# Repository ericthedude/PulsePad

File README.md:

# PulsePad
A macropad made for HackClub's Hackpad project

Incudes 4 reprogrammable macro switches and 1 reprogrammable knob

This is my first time creating something from scratch. This is also my first time using github.

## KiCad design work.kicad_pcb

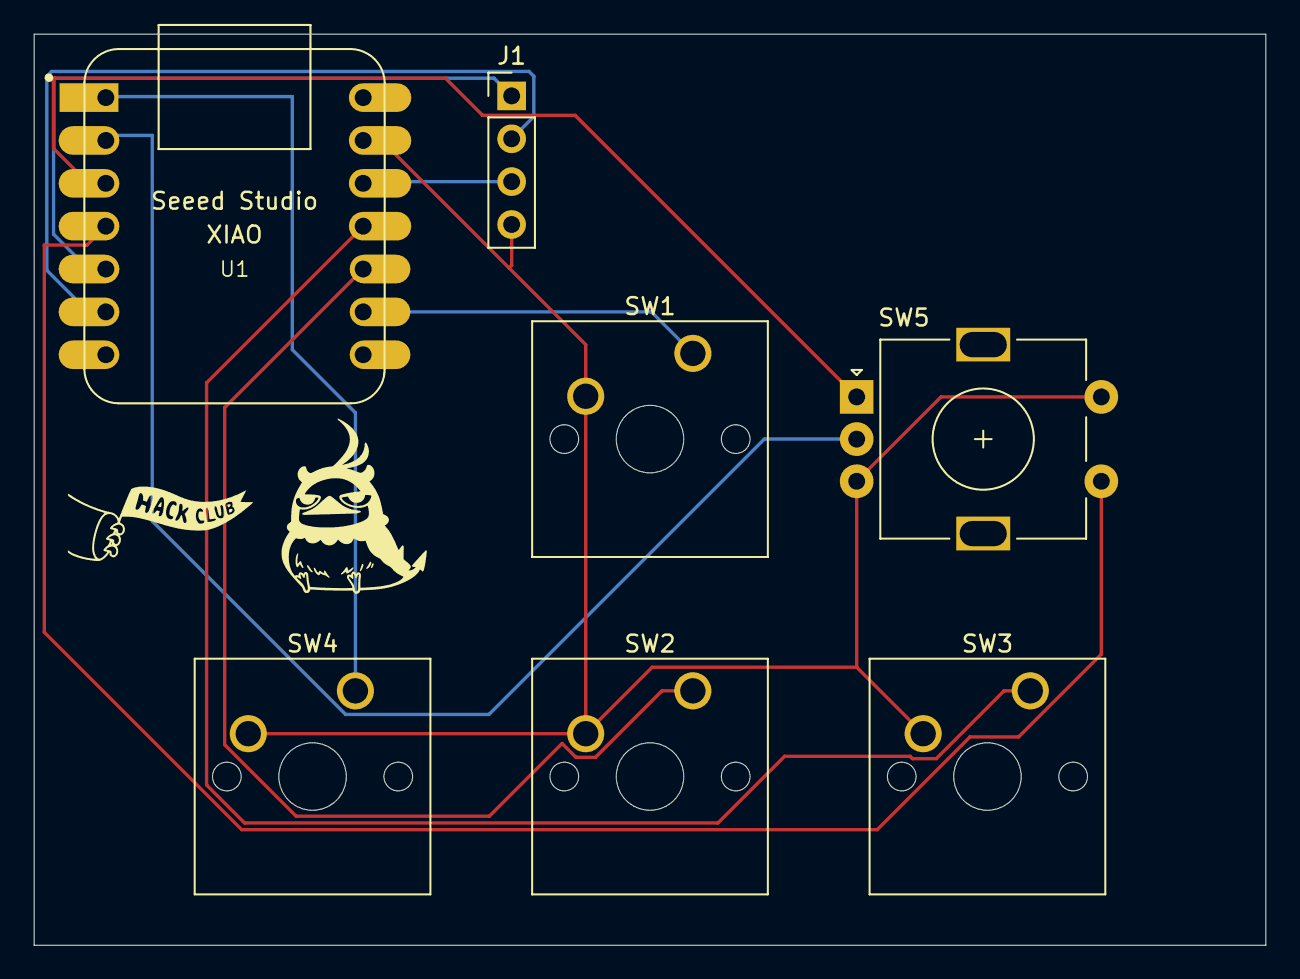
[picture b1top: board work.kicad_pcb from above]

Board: 2 copper layers, 73.0 x 54.0 mm, 7 parts (0 on the bottom side), 11 nets.

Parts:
J1: Conn_01x04_Pin; PinHeader_1x04_P2.54mm_Vertical
SW1: SW_Push_45deg; SW_Cherry_MX_1.00u_PCB
SW2, SW3, SW4: SW_Push_45deg; SW_Cherry_MX_1.50u_PCB
SW5: RotaryEncoder_Switch; RotaryEncoder_Alps_EC11E-Switch_Vertical_H20mm
U1: MOUDLE-SEEEDUINO-XIAO; XIAO-Generic-Hybrid-14P-2.54-21X17.8MM

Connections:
GND: J1.Ground (Pin_4_4), SW1.2, SW2.2, SW3.2, SW4.2, SW5.B, SW5.S2, U1.13 (GND)
unnamed: J1.1 (Pin_1_1), U1.5 (PA8_A4_D4_SDA)
unnamed: J1.2 (Pin_2_2), U1.6 (PA9_A5_D5_SCL)
unnamed: J1.3 (Pin_3_3), U1.12 (3V3)
unnamed: SW4.1, U1.1 (PA02_A0_D0)
unnamed: SW5.C, U1.2 (PA4_A1_D1)
unnamed: SW2.1, U1.10 (PA5_A9_D9_MISO)
unnamed: SW3.1, U1.11 (PA6_A10_D10_MOSI)
unnamed: SW1.1, U1.9 (PA7_A8_D8_SCK)
unnamed: SW5.A, U1.3 (PA10_A2_D2)
unnamed: SW5.S1, U1.4 (PA11_A3_D3)
